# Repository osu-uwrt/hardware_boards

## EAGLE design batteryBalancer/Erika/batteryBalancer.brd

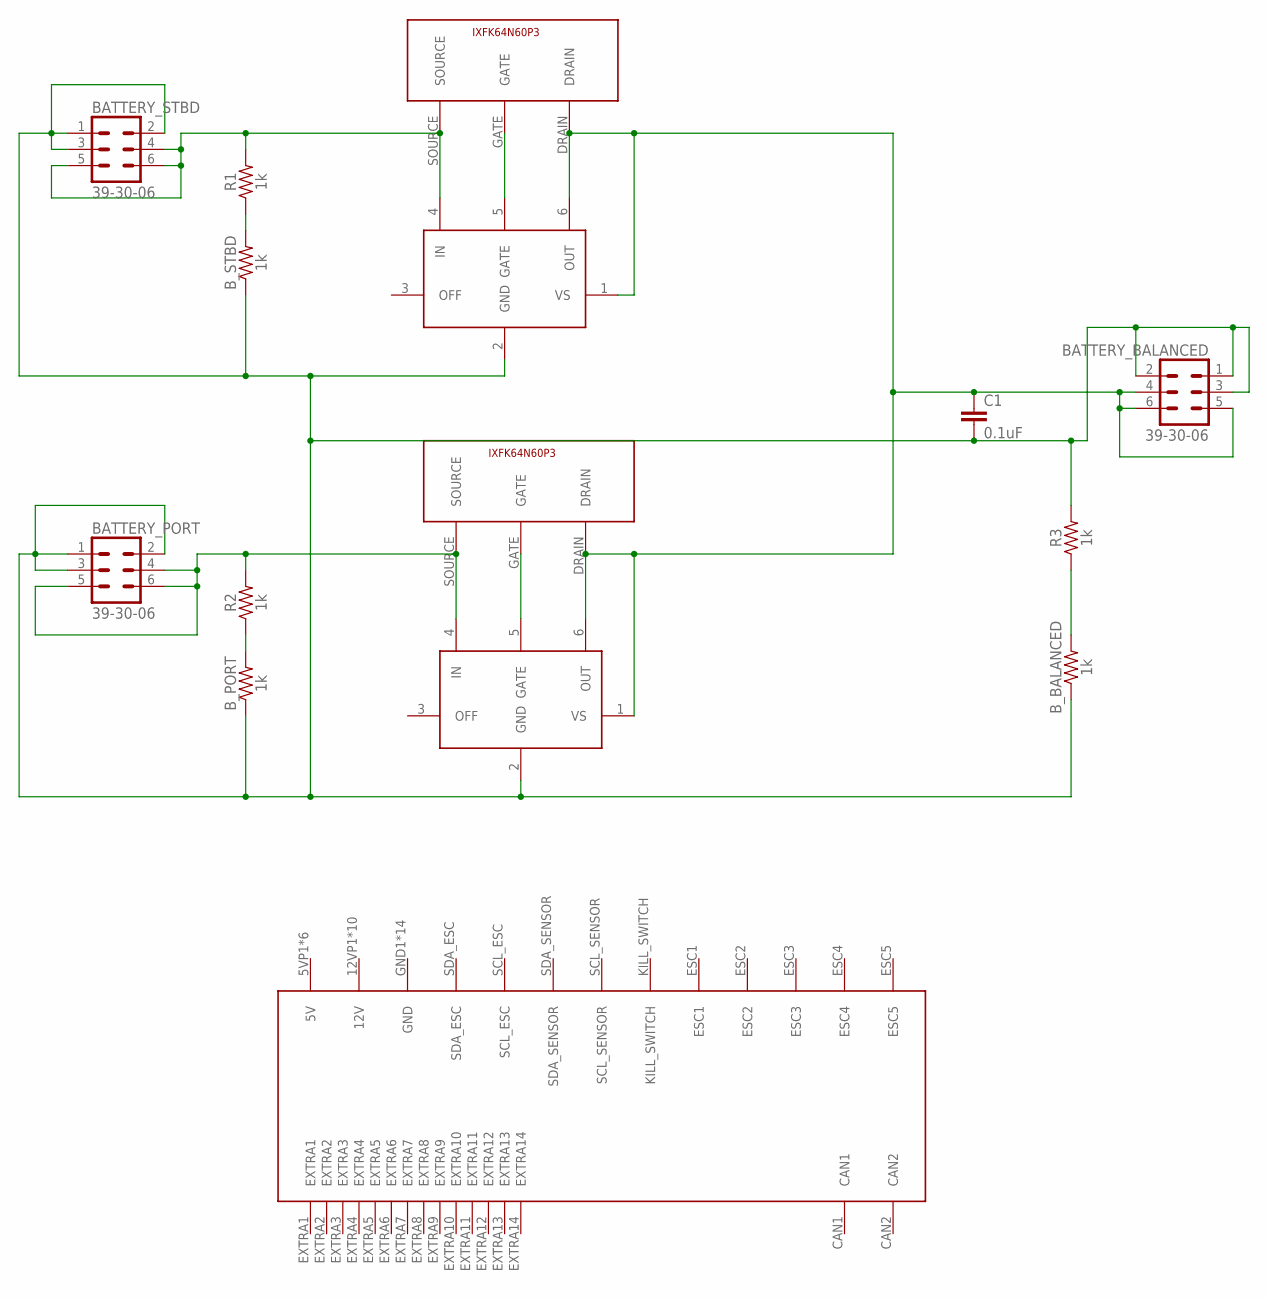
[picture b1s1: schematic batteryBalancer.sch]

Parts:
BATTERY_BALANCED: 39-30-06; 39-30-?06?
BATTERY_PORT: 39-30-06; 39-30-?06?
BATTERY_STBD: 39-30-06; 39-30-?06?
B_BALANCED: 1k; AXIAL-0.3-KIT
B_PORT: 1k; AXIAL-0.3-KIT
B_STBD: 1k; AXIAL-0.3-KIT
C1: 0.1uF; CAP-PTH-SMALL-KIT
MOS_PORT: IXFK64N60P3
MOS_STBD: IXFK64N60P3
R1, R2, R3: 1k; AXIAL-0.3-KIT
U$3, U$4: LM5050-1; SOT23-6
U$5: 5530843; 5530843-6-BOARDFINGERS

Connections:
BALENCED_LOAD: BATTERY_BALANCED.4, BATTERY_BALANCED.5, BATTERY_BALANCED.6, C1.1, MOS_PORT.DRAIN, MOS_STBD.DRAIN, U$3.1 (VS), U$3.6 (OUT), U$4.1 (VS), U$4.6 (OUT)
BAT_GND: BATTERY_BALANCED.1, BATTERY_BALANCED.2, BATTERY_BALANCED.3, BATTERY_PORT.1, BATTERY_PORT.2, BATTERY_PORT.3, BATTERY_STBD.1, BATTERY_STBD.2, BATTERY_STBD.3, B_BALANCED.P$1 (1), B_PORT.P$1 (1), B_STBD.P$1 (1), C1.2, R3.P$2 (2), U$3.2 (GND), U$4.2 (GND)
GATE1: MOS_STBD.GATE, U$3.5 (GATE)
GATE2: MOS_PORT.GATE, U$4.5 (GATE)
LOAD_1: BATTERY_STBD.4, BATTERY_STBD.5, BATTERY_STBD.6, MOS_STBD.SOURCE, R1.P$2 (2), U$3.4 (IN)
LOAD_2: BATTERY_PORT.4, BATTERY_PORT.5, BATTERY_PORT.6, MOS_PORT.SOURCE, R2.P$2 (2), U$4.4 (IN)
unnamed: B_BALANCED.P$2 (2), R3.P$1 (1)
unnamed: B_STBD.P$2 (2), R1.P$1 (1)
unnamed: B_PORT.P$2 (2), R2.P$1 (1)

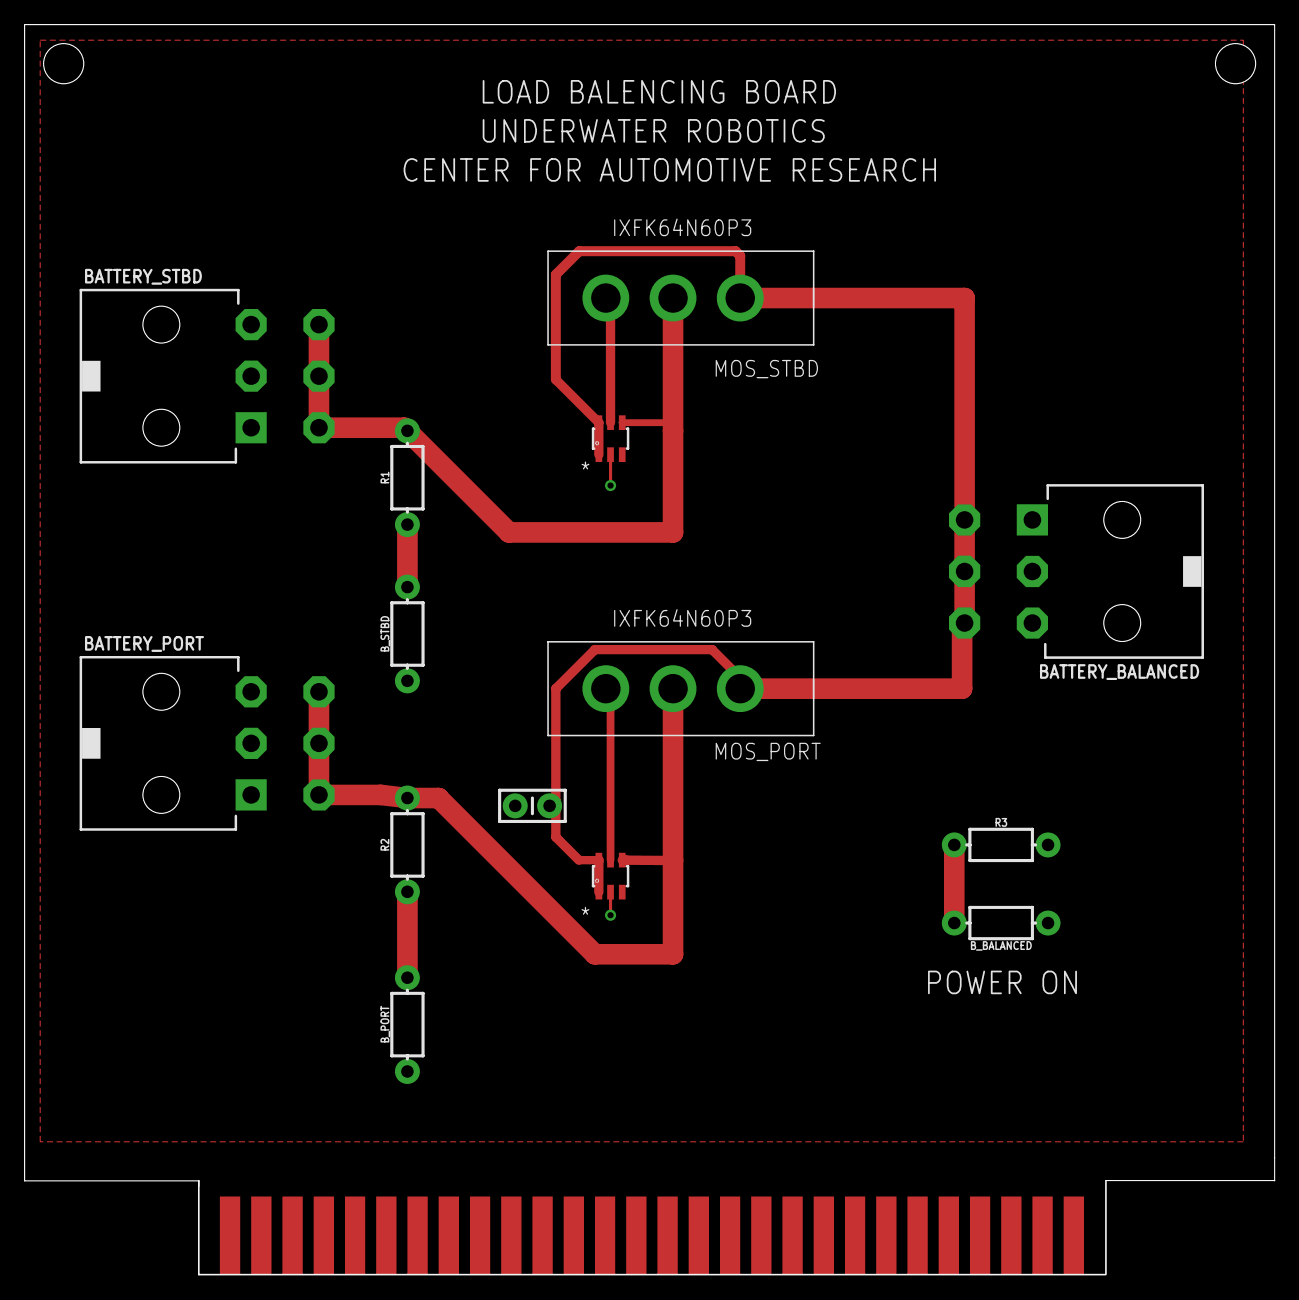
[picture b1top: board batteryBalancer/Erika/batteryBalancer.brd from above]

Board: 2 copper layers, 101.6 x 101.6 mm, 15 parts (0 on the bottom side), 9 nets.

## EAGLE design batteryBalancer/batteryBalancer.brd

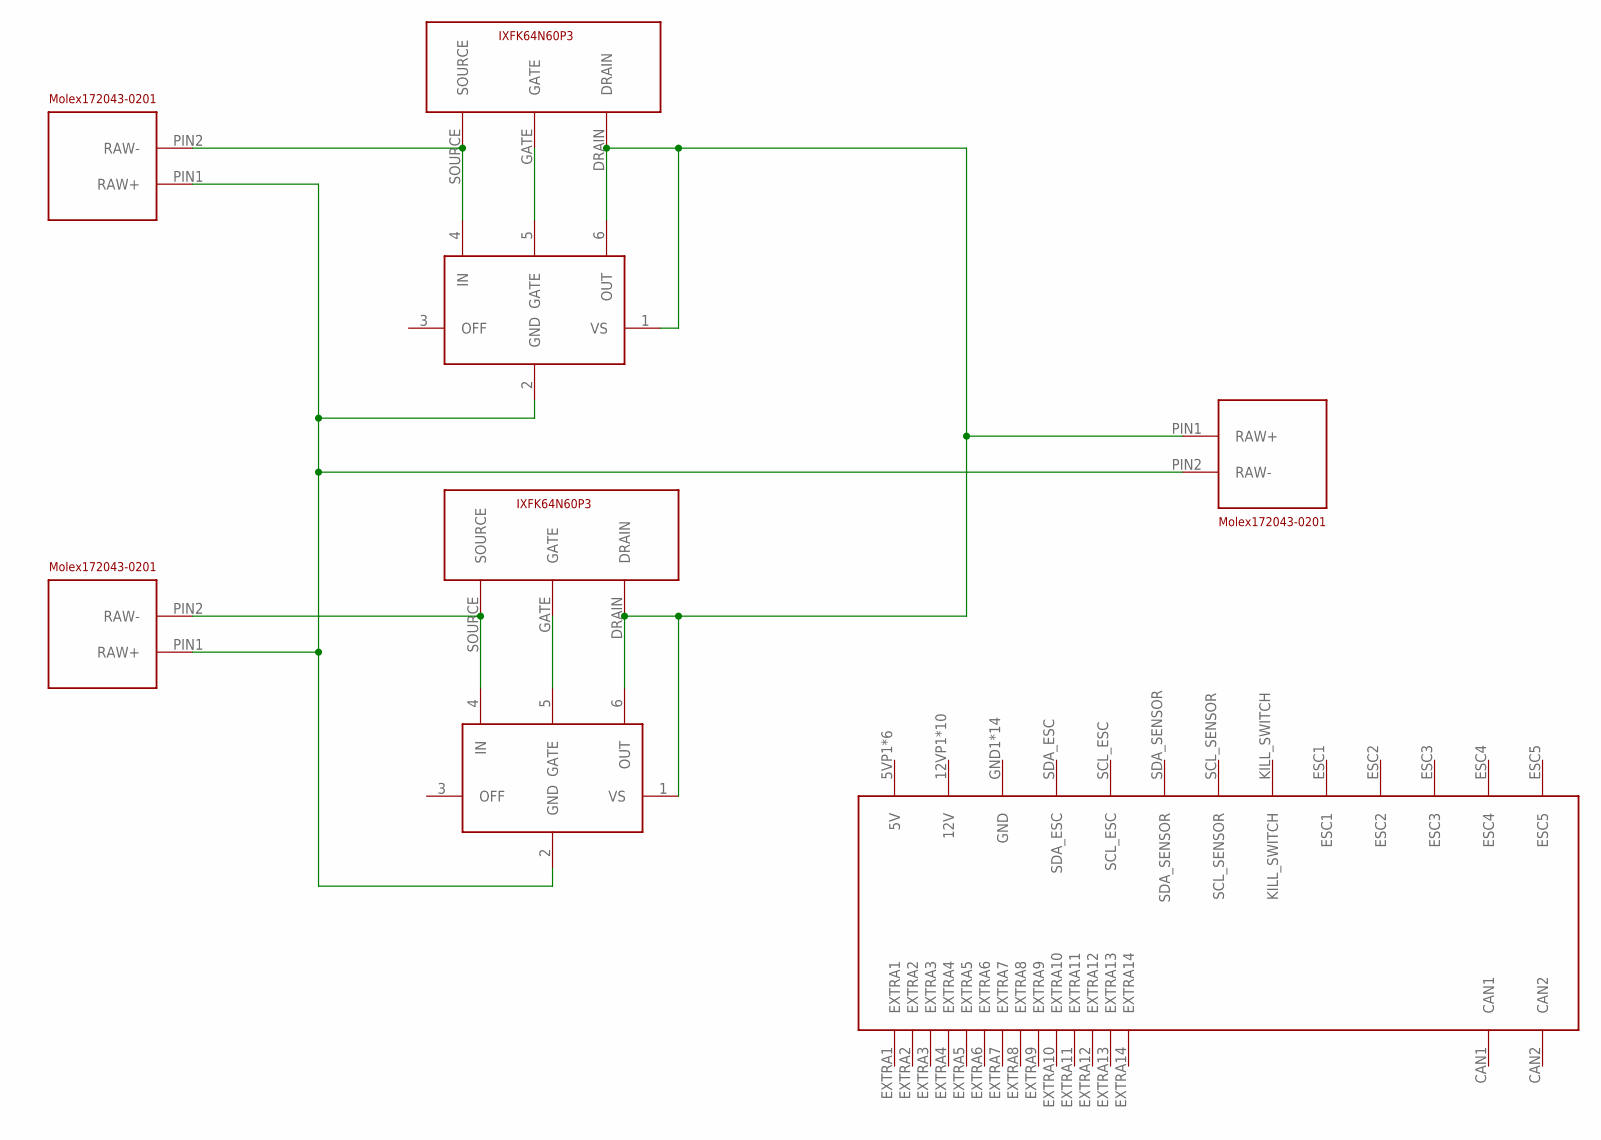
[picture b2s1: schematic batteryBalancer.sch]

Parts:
BAT_IN_1, BAT_IN_2: MOLEX172043-0201
BAT_OUT: MOLEX172043-0201
U$1, U$2: IXFK64N60P3
U$3, U$4: LM5050-1; SOT23-6
U$5: 5530843; 5530843-6-BOARDFINGERS

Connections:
BALENCED_LOAD: BAT_OUT.PIN1 (RAW+), U$1.DRAIN, U$2.DRAIN, U$3.1 (VS), U$3.6 (OUT), U$4.1 (VS), U$4.6 (OUT)
BAT_GND: BAT_IN_1.PIN1 (RAW+), BAT_IN_2.PIN1 (RAW+), BAT_OUT.PIN2 (RAW-), U$3.2 (GND), U$4.2 (GND)
GATE_1: U$1.GATE, U$3.5 (GATE)
LOAD_1: BAT_IN_1.PIN2 (RAW-), U$1.SOURCE, U$3.4 (IN)
LOAD_2: BAT_IN_2.PIN2 (RAW-), U$2.SOURCE, U$4.4 (IN)
unnamed: U$2.GATE, U$4.5 (GATE)

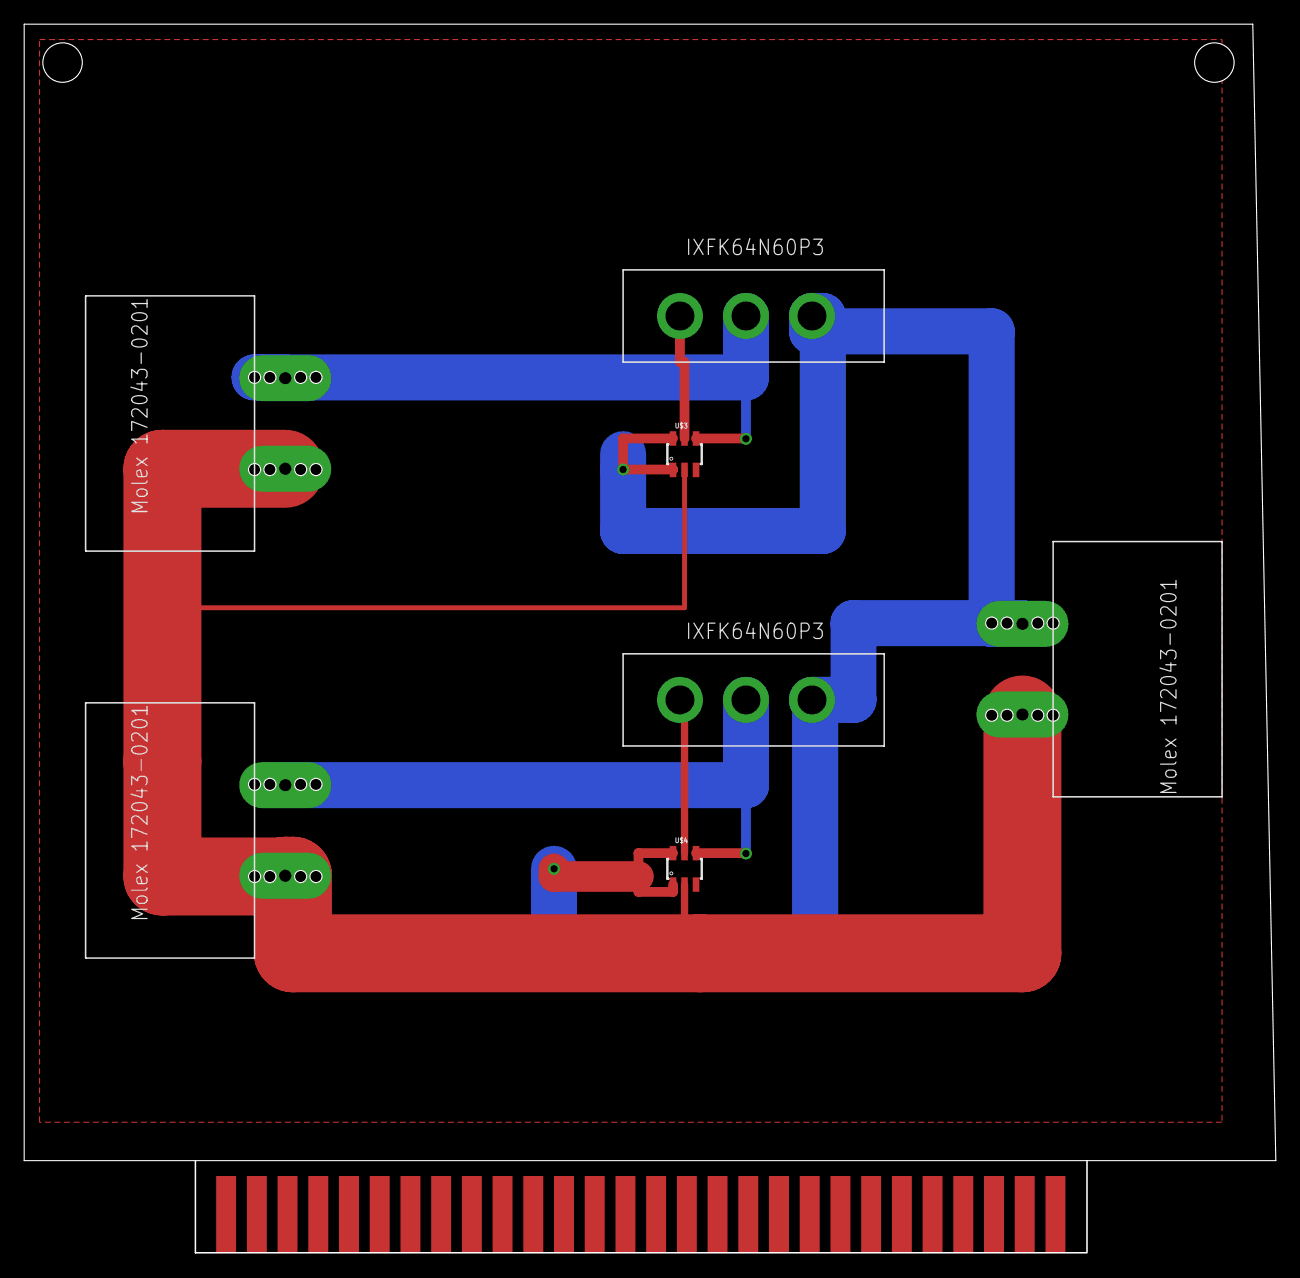
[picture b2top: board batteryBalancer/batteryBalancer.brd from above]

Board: 2 copper layers, 103.5 x 101.6 mm, 8 parts (0 on the bottom side), 6 nets.

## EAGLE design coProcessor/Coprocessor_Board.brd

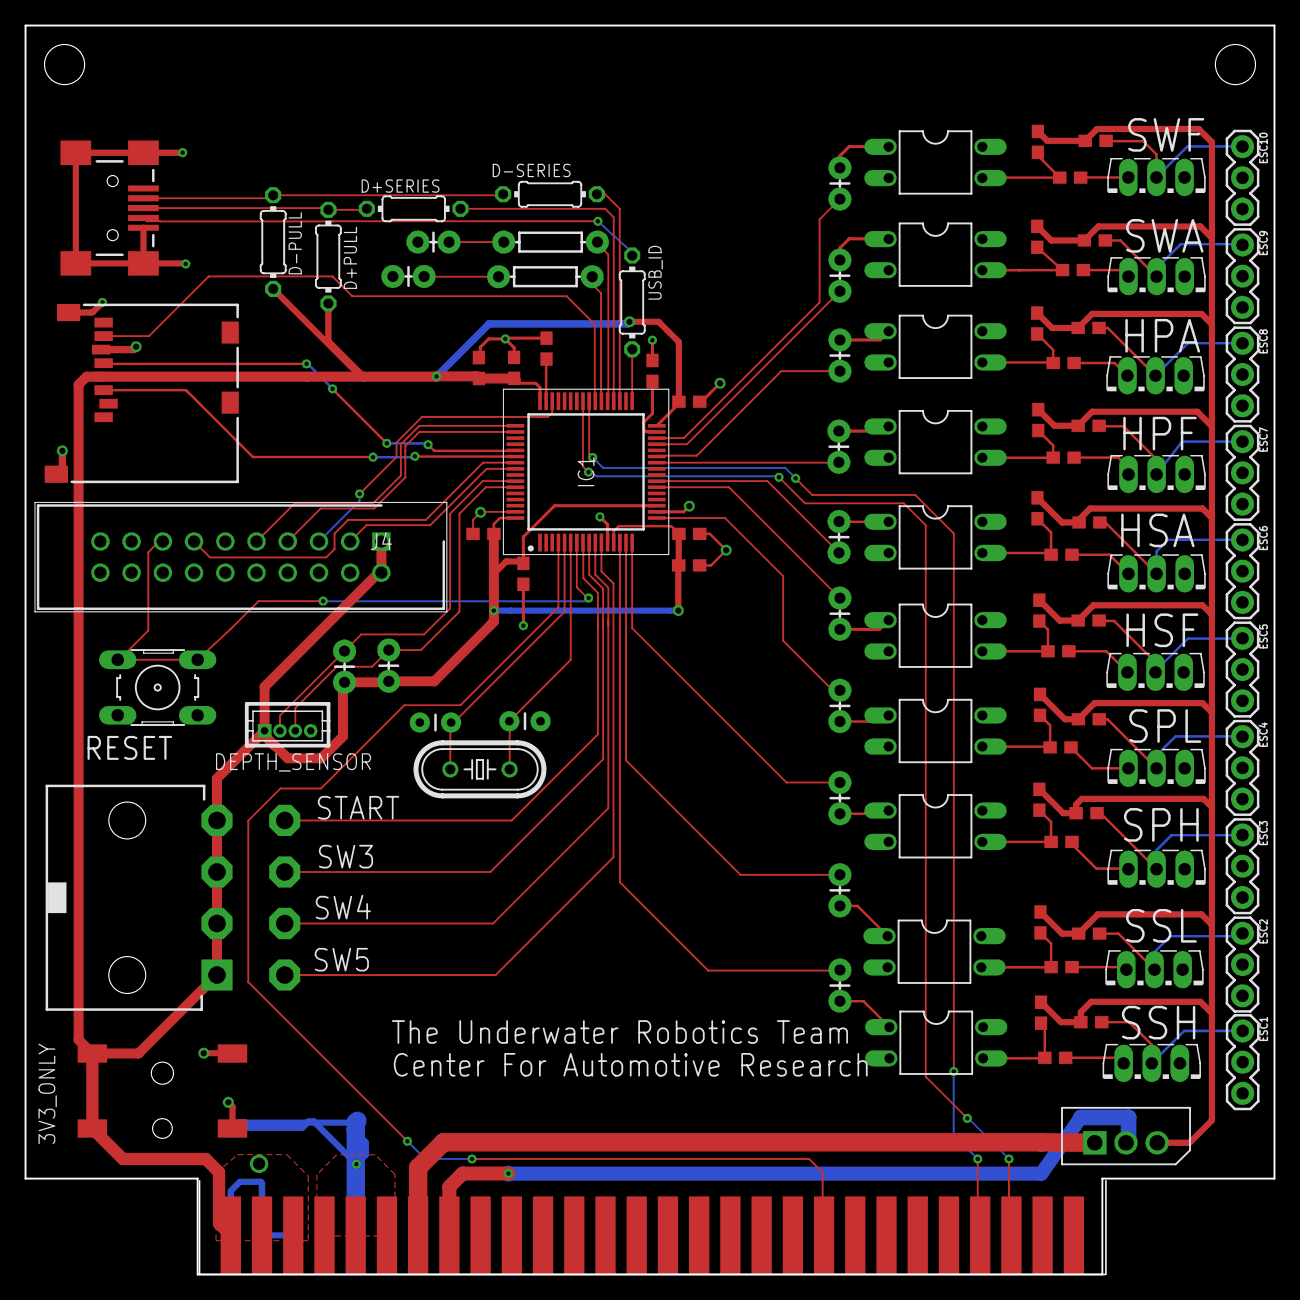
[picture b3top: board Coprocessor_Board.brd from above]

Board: 2 copper layers, 101.6 x 101.6 mm, 103 parts (0 on the bottom side), 87 nets.

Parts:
3V3_ONLY: PJ-002AH-SMT-TR; CUI_PJ-002AH-SMT-TR
C1: 4.7 uF; 0603
C2, C3, C4, C5, C10: 100 nF; 0603
C7: 1 uF; 0603
C8, C9: 1 nF; CAP-PTH-2.54
C11: 2.2uF; 0603
C12: 2.2 uF; 0603
D+PULL: 1.5k; 0204/7
D+SERIES: 22Ω; 0204/7
D-PULL: 1.5k; 0204/7
D-SERIES: 22Ω; 0204/7
DEPTH_SENSOR: DF13-4P-1.25DSA
DS_R1, DS_R2: 4.7k; AXIAL-0.1
ESC1, ESC2, ESC3, ESC4, ESC5, ESC6, ESC7, ESC8, ESC9, ESC10: 1X03
HBL1, HBL2: LED; AXIAL-0.1
IC1: STM32F405RGT6; QFP50P1200X1200X160-64N
J1: USB_MINI-B_SMT; USB-MINIB
J4: 30320-6002HB; SHDR20W81P254_2X10_3300X840X93
J5: 5008730806
OI1, OI2, OI3, OI4, OI5, OI6, OI7, OI8, OI9, OI10: SFH610; DIL04
ORIN1, ORIN2, ORIN3, ORIN4, ORIN5, ORIN6, ORIN7, ORIN8, ORIN9, ORIN10: 220; AXIAL-0.1
OSCILLATOR: HC49/S
P1: 39-30-08?; 39-30-?08?
Q1: L78M05CV; TO254P450X1020X1935-3P
RESET: B3F-10XX
RHB1, RHB2: 1k; AXIAL-0.3
RO1A, RO2A, RO3A, RO4A, RO5A, RO6A, RO7A, RO8A, RO9A, RO10A: 1k; 0603
RO1B, RO1C, RO2B, RO2C, RO3B, RO3C, RO4B, RO4C, RO5B, RO5C, RO6B, RO6C, RO7B, RO7C, RO8B, RO8C, RO9B, RO9C, RO10B, RO10C: 10k; 0603
T1, T2, T3, T4, T5, T6, T7, T8, T9, T10: TO126V
U$1: 5530843; 5530843-6-BOARDFINGERS
USB_ID: 0Ω; 0204/7

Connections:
3.3V: 3V3_ONLY.1.1, 3V3_ONLY.1.2, C1.1, C2.1, C3.1, C4.1, C5.1, C7.1, C10.1, D+PULL.2, D-PULL.2, DEPTH_SENSOR.P$1, DS_R1.P$2, DS_R2.P$2, IC1.13, IC1.19, IC1.32, IC1.48, IC1.64, J4.1, J4.2, J5.4, P1.1, P1.2, P1.3, P1.4, U$1.3.3VP1, U$1.3.3VP2, U$1.3.3VP3, U$1.3.3V_4, U$1.3.3V_5, U$1.3.3V_6
5V: Q1.3, RO1B.2, RO1C.2, RO2B.2, RO2C.2, RO3B.2, RO3C.2, RO4B.2, RO4C.2, RO5B.2, RO5C.2, RO6B.2, RO6C.2, RO7B.2, RO7C.2, RO8B.2, RO8C.2, RO9B.2, RO9C.2, RO10B.2, RO10C.2
18V: Q1.1, U$1.EXTRA23
D+CON: D+PULL.1, D+SERIES.2, J1.D+
D-CON: D-PULL.1, D-SERIES.2, J1.D-
DEPTHSCL: DEPTH_SENSOR.P$2, DS_R2.P$1, IC1.58
DEPTHSDA: DEPTH_SENSOR.P$3, DS_R1.P$1, IC1.59
GATE1: RO1A.1, T1.3
GATE2: RO2A.1, T2.3
GATE3: RO3A.1, T3.3
GATE4: RO4A.1, T4.3
GATE5: RO5A.1, T5.3
GATE6: RO6A.1, T6.3
GATE7: RO7A.1, T7.3
GATE8: RO8A.1, T8.3
GATE9: RO9A.1, T9.3
GATE10: RO10A.1, T10.3
GND: 3V3_ONLY.2, 3V3_ONLY.3, C1.2, C2.2, C3.2, C4.2, C5.2, C7.2, C8.1, C9.1, C10.2, C11.1, C12.2, DEPTH_SENSOR.P$4, HBL1.P$2, HBL2.P$2, IC1.12, IC1.18, IC1.63, J1.GND, J1.S1, J1.S2, J1.S3, J1.S4, J4.4, J4.6, J4.8, J4.10, J4.12, J4.14, J4.16, J4.18, J4.20, J5.6, J5.S3, J5.S4, OI1.2, OI2.2, OI3.2, OI4.2, OI5.2, OI6.2, OI7.2, OI8.2, OI9.2, OI10.2, RESET.2, U$1.GND1, U$1.GND2, U$1.GND3, U$1.GND_4, U$1.GND_5, U$1.GND_6
GNDBAT: ESC1.3, ESC2.3, ESC3.3, ESC4.3, ESC5.3, ESC6.3, ESC7.3, ESC8.3, ESC9.3, ESC10.3, OI1.4, OI2.4, OI3.4, OI4.4, OI5.4, OI6.4, OI7.4, OI8.4, OI9.4, OI10.4, Q1.2, T1.1, T2.1, T3.1, T4.1, T5.1, T6.1, T7.1, T8.1, T9.1, T10.1, U$1.EXTRA24
HEARTBEAT_1: IC1.37, RHB1.P$1
HEARTBEAT_2: IC1.38, RHB2.P$1
HEAVE_PORT_AFT: IC1.27, ORIN8.P$1
HEAVE_PORT_FWD: IC1.26, ORIN7.P$1
HEAVE_STBD_AFT: IC1.23, ORIN6.P$1
HEAVE_STBD_FWD: IC1.22, ORIN5.P$1
JTAG15: IC1.7, J4.15, RESET.3, RESET.4
KILLSWITCH: IC1.4, U$1.KILL_SWITCH
MISSION_START: IC1.8, P1.8
unnamed: HBL1.P$1, RHB1.P$2
unnamed: HBL2.P$1, RHB2.P$2
OTG_ID: IC1.33, USB_ID.1
OTG_ID_CON: J1.ID, USB_ID.2
POWER2O1: OI1.3, RO1A.2, RO1B.1
POWER2O2: OI2.3, RO2A.2, RO2B.1
POWER2O3: OI3.3, RO3A.2, RO3B.1
POWER2O4: OI4.3, RO4A.2, RO4B.1
POWER2O5: OI5.3, RO5A.2, RO5B.1
POWER2O6: OI6.3, RO6A.2, RO6B.1
POWER2O9: OI9.3, RO9A.2, RO9B.1
POWER2O10: OI10.3, RO10A.2, RO10B.1
POWER207: OI7.3, RO7A.2, RO7B.1
POWER208: OI8.3, RO8A.2, RO8B.1
PWM1: OI1.1, ORIN1.P$2
PWM2: OI2.1, ORIN2.P$2
PWM3: OI3.1, ORIN3.P$2
PWM4: OI4.1, ORIN4.P$2
PWM5: OI5.1, ORIN5.P$2
PWM6: OI6.1, ORIN6.P$2
PWM7: OI7.1, ORIN7.P$2
PWM8: OI8.1, ORIN8.P$2
PWM9: OI9.1, ORIN9.P$2
PWM10: OI10.1, ORIN10.P$2
RCC_OSC_IN: C8.2, IC1.5, OSCILLATOR.2
RCC_OSC_OUT: C9.2, IC1.6, OSCILLATOR.1
SCL_BKPLN: IC1.41, U$1.SCL_SENSOR
SDA_BKPLN: IC1.40, U$1.SDA_SENSOR
SDIO_CK: IC1.53, J5.5
SDIO_CMD: IC1.54, J5.3
SDIO_DO: IC1.39, J5.7
SOURCE1: ESC1.1, RO1C.1, T1.2
SOURCE2: ESC2.1, RO2C.1, T2.2
SOURCE3: ESC3.1, RO3C.1, T3.2
SOURCE4: ESC4.1, RO4C.1, T4.2
SOURCE5: ESC5.1, RO5C.1, T5.2
SOURCE6: ESC6.1, RO6C.1, T6.2
SOURCE7: ESC7.1, RO7C.1, T7.2
SOURCE8: ESC8.1, RO8C.1, T8.2
SOURCE9: ESC9.1, RO9C.1, T9.2
SOURCE10: ESC10.1, RO10C.1, T10.2
SURGEPORTHI: IC1.16, ORIN3.P$1
SURGEPORTLOW: IC1.17, ORIN4.P$1
SURGESTBDHI: IC1.14, ORIN1.P$1
SURGESTBDLOW: IC1.15, ORIN2.P$1
SWITCH_3: IC1.9, P1.7
SWITCH_4: IC1.10, P1.6
SWITCH_5: IC1.11, P1.5
SW_AFT: IC1.29, ORIN9.P$1
SW_FWD: IC1.30, ORIN10.P$1
SYS_JTCK-SWCLK: IC1.49, J4.9
SYS_JTDI: IC1.50, J4.7
SYS_JTDO-SWO: IC1.55, J4.13
SYS_JTMS-SWIDIO: IC1.46, J4.5
SYS_JTRST: IC1.56, J4.3
USB_OTG_HS_DM: D-SERIES.1, IC1.35
USB_OTG_HS_DP: D+SERIES.1, IC1.36
VCAP: C11.2, IC1.47
VCAP2: C12.1, IC1.31

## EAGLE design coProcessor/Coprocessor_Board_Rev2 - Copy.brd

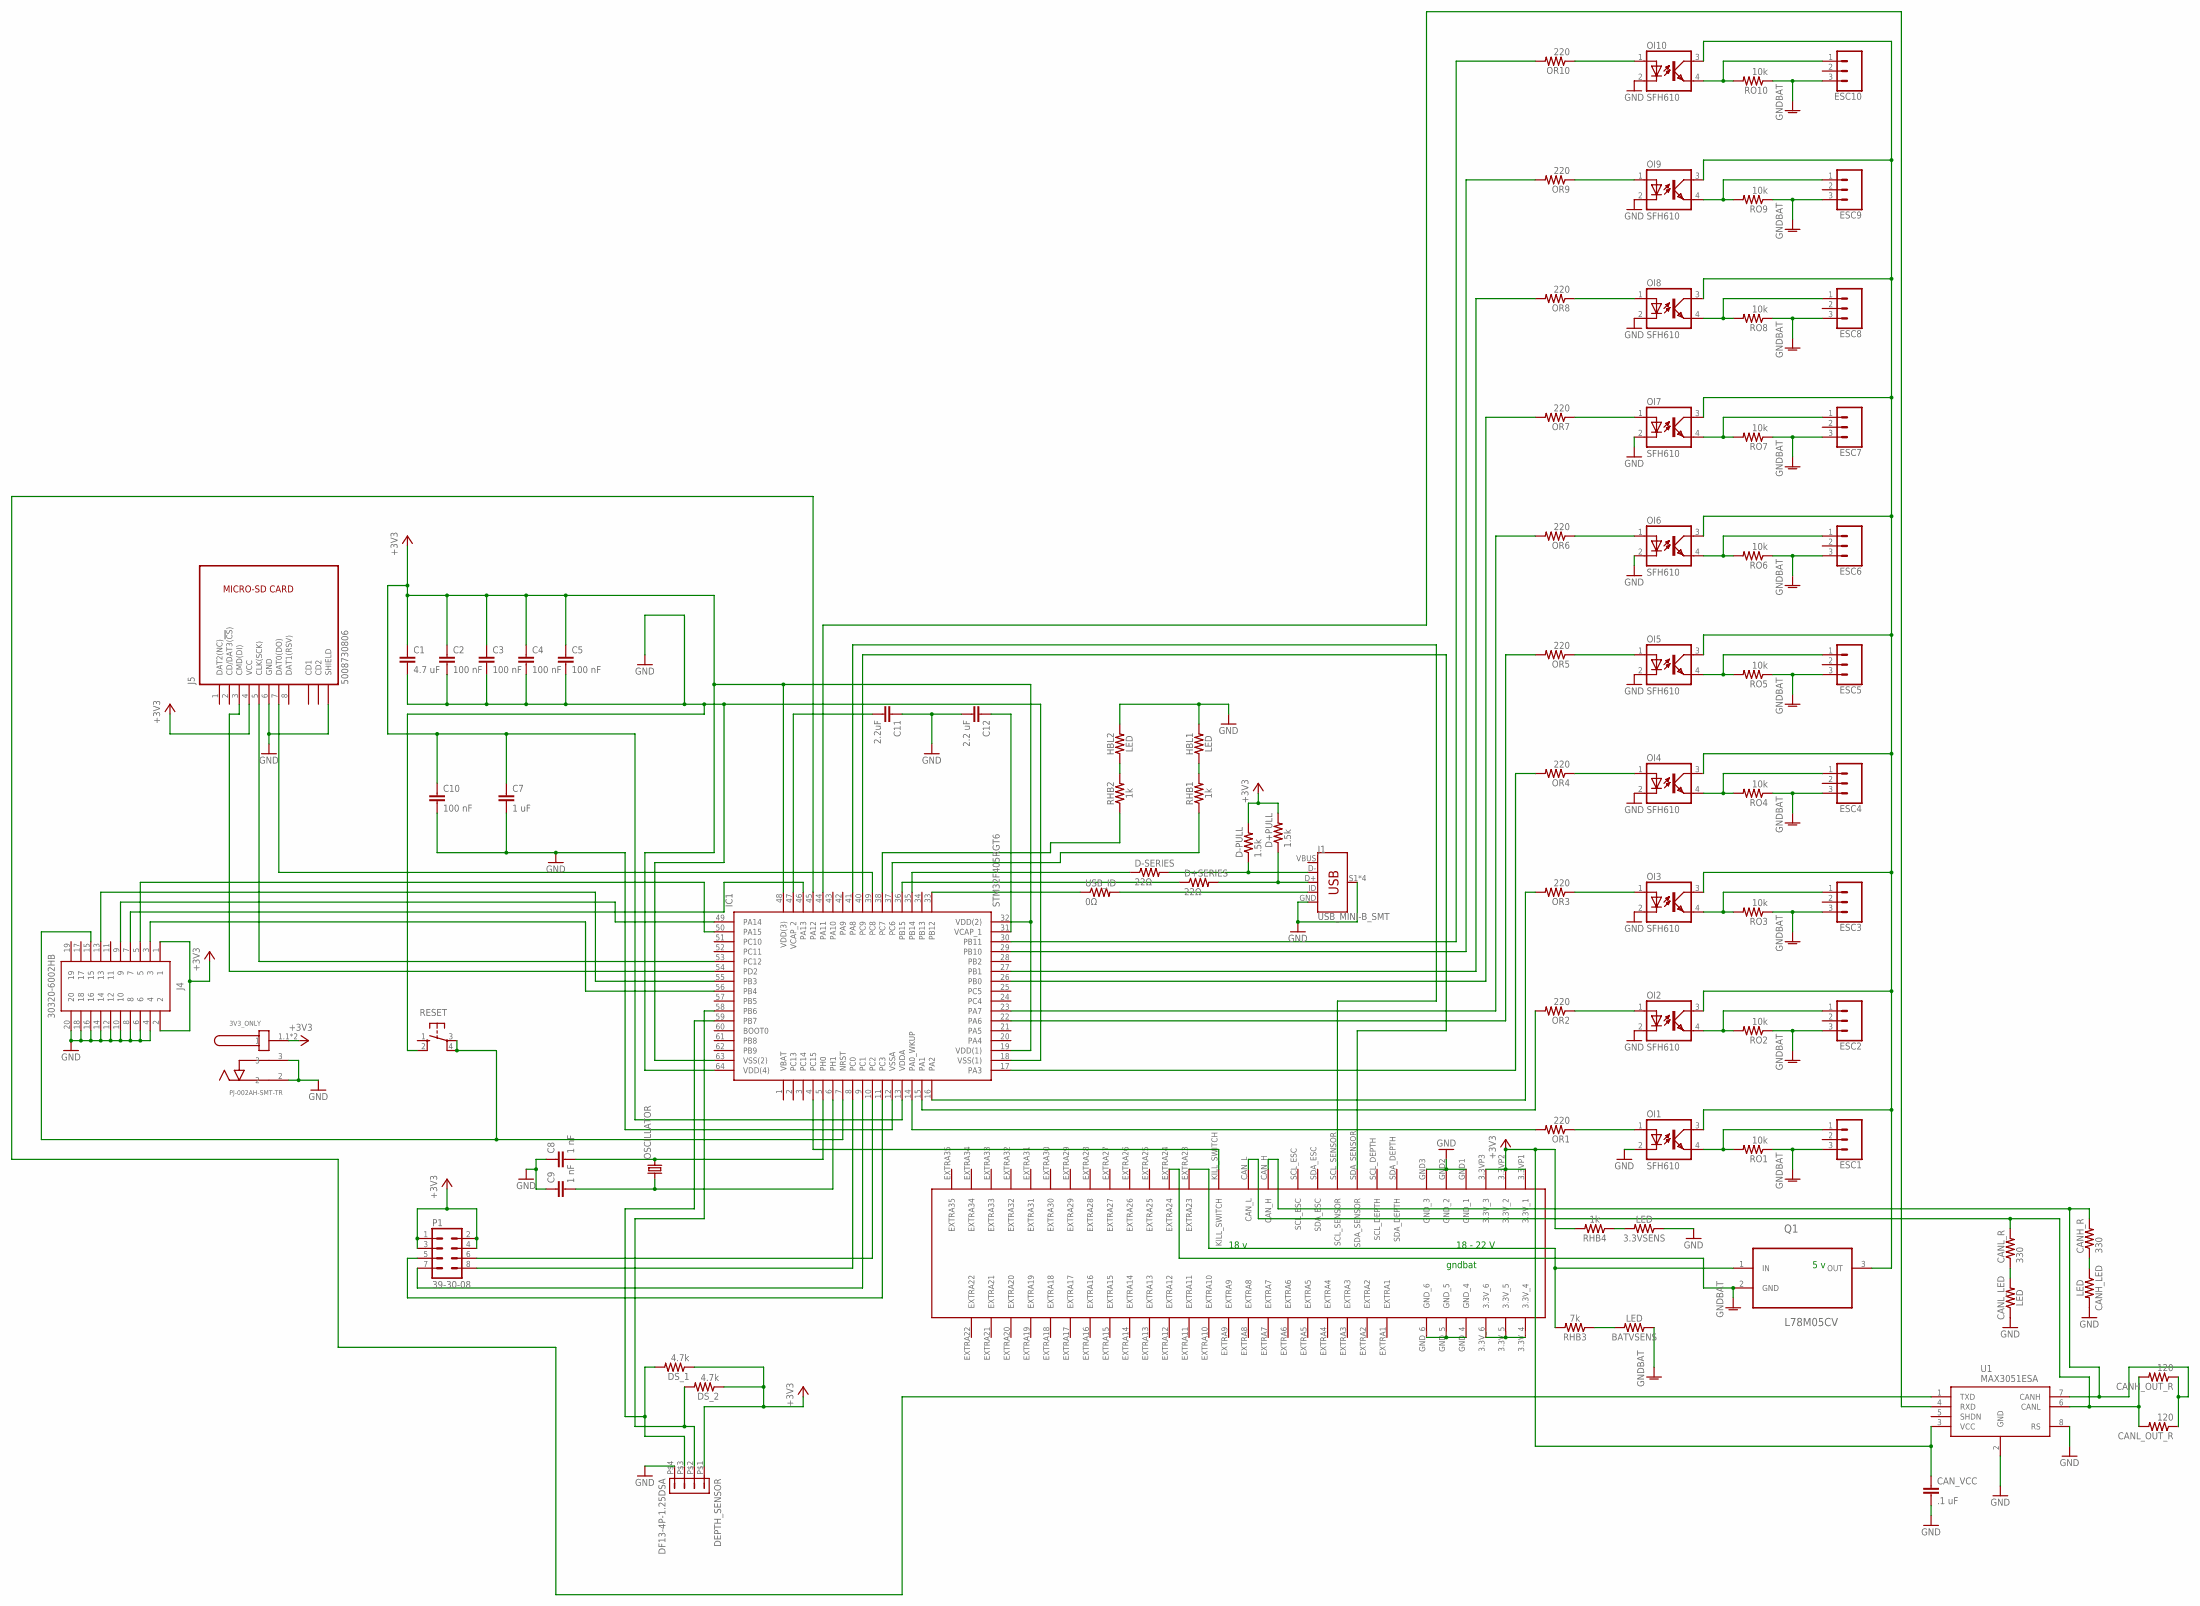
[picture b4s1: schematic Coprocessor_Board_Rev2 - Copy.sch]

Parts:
3.3VSENS: LED; AXIAL-0.1
3V3_ONLY: PJ-002AH-SMT-TR; CUI_PJ-002AH-SMT-TR
BATVSENS: LED; AXIAL-0.1
C1: 4.7 uF; 0603
C2, C3, C4, C5, C10: 100 nF; 0603
C7: 1 uF; 0603
C8, C9: 1 nF; CAP-PTH-2.54
C11: 2.2uF; 0603
C12: 2.2 uF; 0603
CANH_LED: LED; AXIAL-0.1
CANH_OUT_R: 120; 0204/7
CANH_R: 330; 0204/7
CANL_LED: LED; AXIAL-0.1
CANL_OUT_R: 120; 0204/7
CANL_R: 330; 0204/7
CAN_VCC: .1 uF; CAP-PTH-2.54
D+PULL: 1.5k; 0204/7
D+SERIES: 22Ω; 0204/7
D-PULL: 1.5k; 0204/7
D-SERIES: 22Ω; 0204/7
DEPTH_SENSOR: DF13-4P-1.25DSA
DS_1, DS_2: 4.7k; 0204/7
ESC1, ESC2, ESC3, ESC4, ESC5, ESC6, ESC7, ESC8, ESC9, ESC10: CONN_03; 1X03
HBL1, HBL2: LED; AXIAL-0.1
IC1: STM32F405RGT6; QFP50P1200X1200X160-64N
J1: USB_MINI-B_SMT; USB-MINIB
J4: 30320-6002HB; SHDR20W81P254_2X10_3300X840X93
J5: 5008730806
OI1, OI2, OI3, OI4, OI5, OI6, OI7, OI8, OI9, OI10: SFH610; DIL04
OR1, OR2, OR3, OR4, OR5, OR6, OR7, OR8, OR9, OR10: 220; 0204/7
OSCILLATOR: CRYSTALHC49S; HC49/S
P1: 39-30-08; 39-30-?08?
Q1: L78M05CV; TO254P450X1020X1935-3P
RESET: 10-XX; B3F-10XX
RHB1, RHB2, RHB4: 1k; AXIAL-0.3
RHB3: 7k; AXIAL-0.3
RO1, RO2, RO3, RO4, RO5, RO6, RO7, RO8, RO9, RO10: 10k; 0204/7
U1: MAX3051ESA; 8-SOICN
U$1: 5530843; 5530843-6-BOARDFINGERS
USB_ID: 0Ω; 0204/7

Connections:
3.3V: 3V3_ONLY.1.1 (1), 3V3_ONLY.1.2 (1), C1.1, C2.1, C3.1, C4.1, C5.1, C7.1, C10.1, CAN_VCC.1, D+PULL.2, D-PULL.2, DEPTH_SENSOR.P$1 (1), DS_1.1, DS_2.1, IC1.13 (VDDA), IC1.19 (VDD(1)), IC1.32 (VDD(2)), IC1.48 (VDD(3)), IC1.64 (VDD(4)), J4.1, J4.2, J5.4 (VCC), P1.1, P1.2, P1.3, P1.4, RHB4.P$2 (2), U1.3 (VCC), U$1.3.3VP1 (3.3V_1), U$1.3.3VP2 (3.3V_2), U$1.3.3VP3 (3.3V_3), U$1.3.3V_4, U$1.3.3V_5, U$1.3.3V_6
5V: OI1.3 (COL), OI2.3 (COL), OI3.3 (COL), OI4.3 (COL), OI5.3 (COL), OI6.3 (COL), OI7.3 (COL), OI8.3 (COL), OI9.3 (COL), OI10.3 (COL), Q1.3 (OUT)
18V: Q1.1 (IN), RHB3.P$2 (2), U$1.EXTRA23
CAN1_RXD: IC1.44 (PA11), U1.4 (RXD)
CAN1_TXD: IC1.45 (PA12), U1.1 (TXD)
CANH: CANH_OUT_R.1, CANH_R.2, CANL_OUT_R.1, U1.7 (CANH), U$1.CAN_H
CANL: CANH_OUT_R.2, CANL_OUT_R.2, CANL_R.2, U1.6 (CANL), U$1.CAN_L
D+CON: D+PULL.1, D+SERIES.2, J1.D+
D-CON: D-PULL.1, D-SERIES.2, J1.D-
DEPTHSCL: DEPTH_SENSOR.P$2 (2), DS_2.2, IC1.58 (PB6)
DEPTHSDA: DEPTH_SENSOR.P$3 (3), DS_1.2, IC1.59 (PB7)
GND: 3V3_ONLY.2, 3V3_ONLY.3, C1.2, C2.2, C3.2, C4.2, C5.2, C7.2, C8.1, C9.1, C10.2, C11.1, C12.2, CANH_LED.P$2 (2), CANL_LED.P$1 (1), CAN_VCC.2, DEPTH_SENSOR.P$4 (4), HBL1.P$2 (2), HBL2.P$2 (2), IC1.12 (VSSA), IC1.18 (VSS(1)), IC1.63 (VSS(2)), J1.GND, J1.S1 (SHIELD), J1.S2 (SHIELD), J1.S3 (SHIELD), J1.S4 (SHIELD), J4.4, J4.6, J4.8, J4.10, J4.12, J4.14, J4.16, J4.18, J4.20, J5.6 (GND), J5.S3 (SHIELD), J5.S4 (SHIELD), OI1.2 (C), OI2.2 (C), OI3.2 (C), OI4.2 (C), OI5.2 (C), OI6.2 (C), OI7.2 (C), OI8.2 (C), OI9.2 (C), OI10.2 (C), RESET.2 (S1), U1.2 (GND), U1.8 (RS), U$1.GND1 (GND_1), U$1.GND2 (GND_2), U$1.GND3 (GND_3), U$1.GND_4, U$1.GND_5, U$1.GND_6
GNDA: BATVSENS.P$1 (1)
GNDBAT: ESC1.3, ESC2.3, ESC3.3, ESC4.3, ESC5.3, ESC6.3, ESC7.3, ESC8.3, ESC9.3, ESC10.3, Q1.2 (GND), RO1.1, RO2.1, RO3.1, RO4.1, RO5.1, RO6.1, RO7.1, RO8.1, RO9.1, RO10.1, U$1.EXTRA24
HEARTBEAT_1: IC1.37 (PC6), RHB1.P$1 (1)
HEARTBEAT_2: IC1.38 (PC7), RHB2.P$1 (1)
HEAVE_PORT_AFT: IC1.27 (PB1), OR8.2
HEAVE_PORT_FWD: IC1.26 (PB0), OR7.2
HEAVE_STBD_AFT: IC1.23 (PA7), OR6.2
HEAVE_STBD_FWD: IC1.22 (PA6), OR5.2
JTAG15: IC1.7 (NRST), J4.15, RESET.3, RESET.4 (P1)
KILLSWITCH: IC1.4 (PC15), U$1.KILL_SWITCH
MISSION_START: IC1.8 (PC0), P1.8
unnamed: HBL1.P$1 (1), RHB1.P$2 (2)
unnamed: BATVSENS.P$2 (2), RHB3.P$1 (1)
unnamed: 3.3VSENS.P$2 (2), RHB4.P$1 (1)
unnamed: CANH_LED.P$1 (1), CANH_R.1
unnamed: CANL_LED.P$2 (2), CANL_R.1
unnamed: HBL2.P$1 (1), RHB2.P$2 (2)
OTG_ID: IC1.33 (PB12), USB_ID.1
OTG_ID_CON: J1.ID, USB_ID.2
PWM1: OI1.1 (A), OR1.1
PWM2: OI2.1 (A), OR2.1
PWM3: OI3.1 (A), OR3.1
PWM4: OI4.1 (A), OR4.1
PWM5: OI5.1 (A), OR5.1
PWM5V1: ESC1.1, OI1.4 (EMIT), RO1.2
PWM5V2: ESC2.1, OI2.4 (EMIT), RO2.2
PWM5V3: ESC3.1, OI3.4 (EMIT), RO3.2
PWM5V4: ESC4.1, OI4.4 (EMIT), RO4.2
PWM5V5: ESC5.1, OI5.4 (EMIT), RO5.2
PWM5V6: ESC6.1, OI6.4 (EMIT), RO6.2
PWM5V7: ESC7.1, OI7.4 (EMIT), RO7.2
PWM5V8: ESC8.1, OI8.4 (EMIT), RO8.2
PWM5V9: ESC9.1, OI9.4 (EMIT), RO9.2
PWM5V10: ESC10.1, OI10.4 (EMIT), RO10.2
PWM6: OI6.1 (A), OR6.1
PWM7: OI7.1 (A), OR7.1
PWM8: OI8.1 (A), OR8.1
PWM9: OI9.1 (A), OR9.1
PWM10: OI10.1 (A), OR10.1
RCC_OSC_IN: C8.2, IC1.5 (PH0), OSCILLATOR.2
RCC_OSC_OUT: C9.2, IC1.6 (PH1), OSCILLATOR.1
SCL_BKPLN: IC1.41 (PA8), U$1.SCL_SENSOR
SDA_BKPLN: IC1.40 (PC9), U$1.SDA_SENSOR
SDIO_CK: IC1.53 (PC12), J5.5 (CLK(SCK))
SDIO_CMD: IC1.54 (PD2), J5.3 (CMD(DI))
SDIO_DO: IC1.39 (PC8), J5.7 (DAT0(DO))
SURGEPORTHI: IC1.16 (PA2), OR3.2
SURGEPORTLOW: IC1.17 (PA3), OR4.2
SURGESTBDHI: IC1.14 (PA0_WKUP), OR1.2
SURGESTBDLOW: IC1.15 (PA1), OR2.2
SWITCH_3: IC1.9 (PC1), P1.7
SWITCH_4: IC1.10 (PC2), P1.6
SWITCH_5: IC1.11 (PC3), P1.5
SW_AFT: IC1.29 (PB10), OR9.2
SW_FWD: IC1.30 (PB11), OR10.2
SYS_JTCK-SWCLK: IC1.49 (PA14), J4.9
SYS_JTDI: IC1.46 (PA13), J4.7
SYS_JTDO-SWO: IC1.55 (PB3), J4.13
SYS_JTMS-SWIDIO: IC1.50 (PA15), J4.5
SYS_JTRST: IC1.56 (PB4), J4.3
USB_OTG_HS_DM: D-SERIES.1, IC1.35 (PB14)
USB_OTG_HS_DP: D+SERIES.1, IC1.36 (PB15)
VBUS: J1.VBUS
VCAP: C11.2, IC1.47 (VCAP_2)
VCAP2: C12.1, IC1.31 (VCAP_1)

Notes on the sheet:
5 v
18 - 22 V
18 v
gndbat

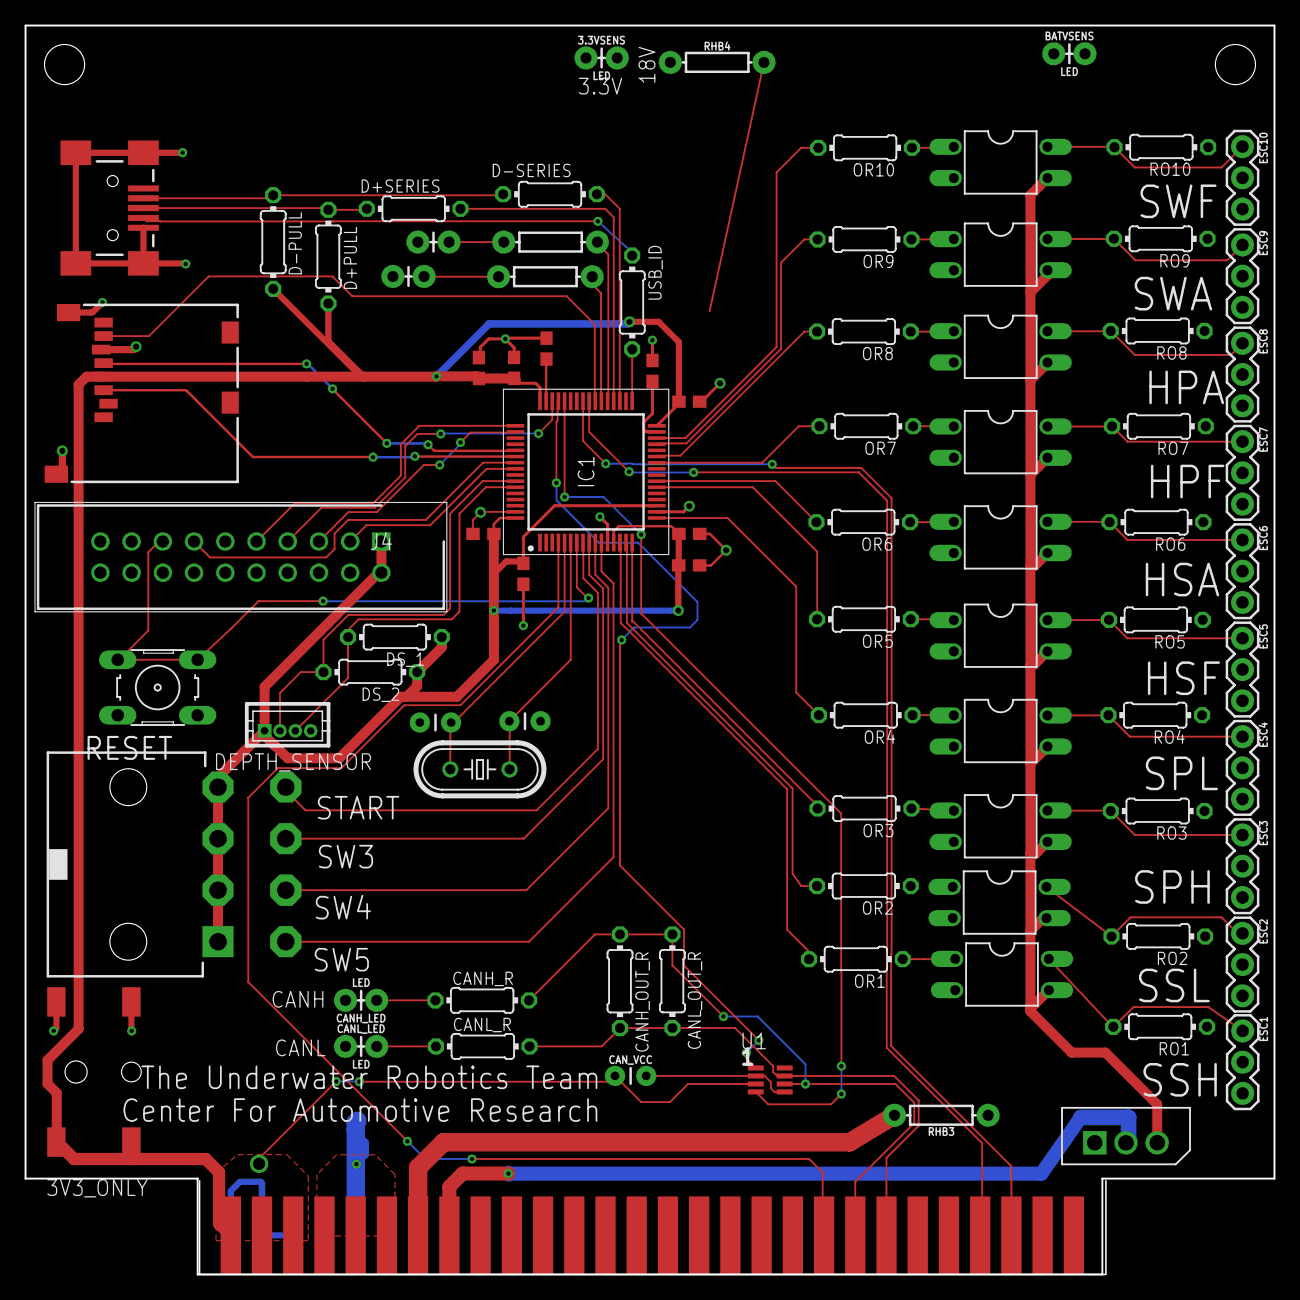
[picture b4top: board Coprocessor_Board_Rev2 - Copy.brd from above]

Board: 2 copper layers, 101.6 x 101.6 mm, 85 parts (0 on the bottom side), 75 nets.

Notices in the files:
parts and their libraries:
con-molex-mini-fit: Copyright (C) 2011, Bob Starr
SparkFun-Capacitors: Licensing: Creative Commons ShareAlike 4.0 International - https://creativecommons.org/licenses/by-sa/4.0
con-molex-milli-grid: Copyright (C) 2010, Bob Starr
